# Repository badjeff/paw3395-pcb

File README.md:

# PAW3395 PCB

PixArt [**PAW3395DM-T6QU**](https://www.pixart.com/products-detail/129/PAW3395DM-T6QU) low power laser mouse sensor breakout board.

- Compatible to **PAW3950DM-T5QU**.
- Be operated with 3.3V voltage level ONLY.
- Outlined as narrow as possible for side mount horizontally and perpendicular on low profile keyboards.
- Developed for [zmk-paw3395-driver](https://github.com/badjeff/zmk-paw3395-driver) and [zmk-paw3950-driver](https://github.com/badjeff/zmk-paw3950-driver)

*Figure 1: Size comparing to Seeed XIAO BLE*

## PCB

Online preview avaliable [here](https://kicanvas.org/?github=https%3A%2F%2Fgithub.com%2Fbadjeff%2Fpaw3395-pcb), powered by [KiCanvas](https://github.com/theacodes/kicanvas).

*Figure 2: PCB edgecuts dimension*

*Figure 3: PCB 3D View - 1.6mm FR4*

### BOM

|Designator|Footprint|Quantity|Value|LCSC Part #|
|-|-|-|-|-|
|C1|SMD 0603|1|4.7uF||
|C11, C9|SMD 0603|2|1uF||
|C2, C4, C5|SMD 0603|3|100nF||
|C3, C6, C8|SMD 0603|3|10uF||
|C7|SMD 0603|1|22uF||
|C10|SMD 0603|1|DNI||
|R1|SMD 0603|1|10K|C25804|
|R2|SMD 0603|1|4.7|C23164|
|R3|SMD 0603|1|2M|C22976|
|U1|SOT-23-5|1|TLV74318PDBVR||
|U2|PAW3395DM-T6QU|1|PAW3395||
|  |PAW3950DM-T5QU|1|PAW3950||

- DNI: don't install.
- SMD 0603 (Imperial) aka 1608 Metric.
- ~~`U1` LDO can be replace by RT9193-18GB, change `C10` to 22nF.~~
- `U1` LDO can be replace by XC6219B182MR or TLV75519PDBVR
- `C1` can be replace by 3.3uF.
- For **PAW3395** Option
  * PAW3395DM-T6QU needs to be used with *compact* LOAE-LSI1 lens, or *chonky* LM19-LSI lens.
- For **PAW3950** Option
  * PAW3950DM-T5QU needs to be used with *compact* LOAE-LSI1 lens, or *chonky* LM19-LSI lens.
  * `R1` should be DNI
  * `R2` should be closed (with zero ohm resistor)
  * Pin 2 & 3 should be connecting with a 2.2uf capicator

*Figure 4: PAW3950 option

### Board Characteristics

- Copper layer count: 2
- Board thickness: 1.6 mm
- Board overall dimensions: 15.5 x 28 mm

### Voltage level config

- 3.3V logic
- VIN: 3.3V

## License

Available under the [CERN-OHL-P v2](/LICENSE) permissive license.

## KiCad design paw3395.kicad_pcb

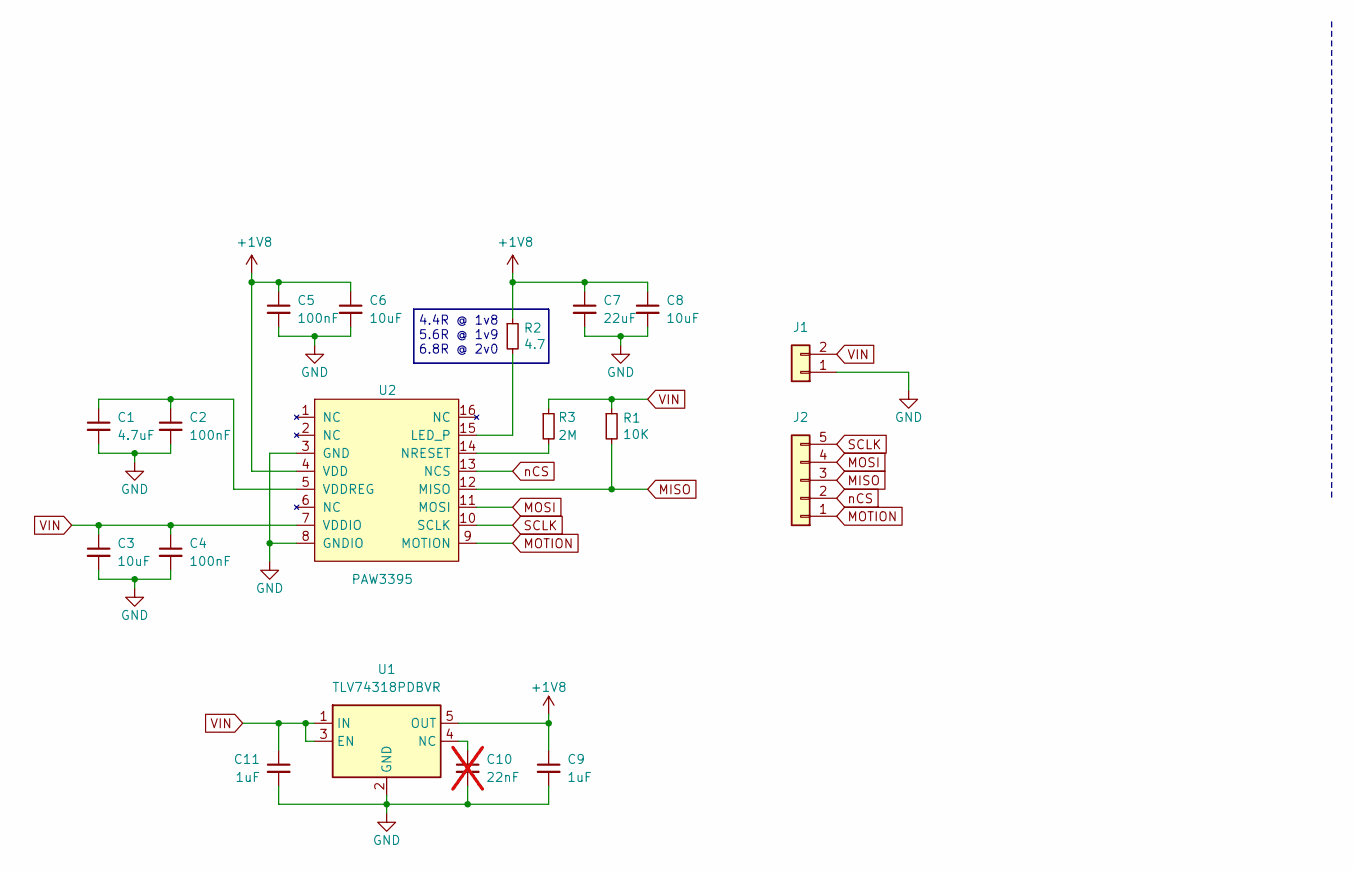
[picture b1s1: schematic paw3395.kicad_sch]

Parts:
C1: 4.7uF; C_0603_1608Metric
C2, C4, C5: 100nF; C_0603_1608Metric
C3, C6, C8: 10uF; C_0603_1608Metric
C7: 22uF; C_0603_1608Metric
C9, C11: 1uF; C_0603_1608Metric
C10: 22nF; C_0603_1608Metric; not fitted
J1: Conn_01x02; PinHeader_1x02_P2.54mm_Vertical
J2: Conn_01x05; PinHeader_1x05_P2.54mm_Vertical
R1: 10K; R_0603_1608Metric; LCSC C25804
R2: 4.7; R_0603_1608Metric; LCSC C23164
R3: 2M; R_0603_1608Metric; LCSC C22976
U1: TLV74318PDBVR; SOT-23-5_HandSoldering
U2: PAW3395

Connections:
+1V8: C5.1, C6.1, C7.1, C8.1, C9.1, R2.1, U1.5 (OUT), U2.4 (VDD)
GND: C1.2, C2.2, C3.2, C4.2, C5.2, C6.2, C7.2, C8.2, C9.2, C10.2, C11.2, J1.1, U1.2 (GND), U2.3 (GND), U2.8 (GNDIO)
MISO: J2.3, R1.2, U2.12 (MISO)
MOSI: J2.4, U2.11 (MOSI)
MOTION: J2.1, U2.9 (MOTION)
unnamed: C10.1, U1.4 (NC)
unnamed: R2.2, U2.15 (LED_P)
unnamed: R3.2, U2.14 (NRESET)
unnamed: C1.1, C2.1, U2.5 (VDDREG)
SCLK: J2.5, U2.10 (SCLK)
VIN: C3.1, C4.1, C11.1, J1.2, R1.1, R3.1, U1.1 (IN), U1.3 (EN), U2.7 (VDDIO)
nCS: J2.2, U2.13 (NCS)

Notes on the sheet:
4.4R @ 1v8 5.6R @ 1v9 6.8R @ 2v0

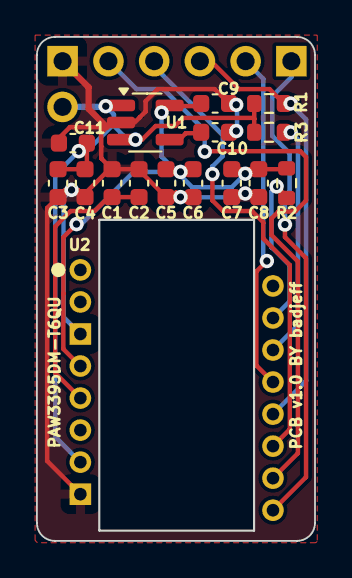
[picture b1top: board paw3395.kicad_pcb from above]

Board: 2 copper layers, 15.4 x 28.0 mm, 18 parts (0 on the bottom side), 12 nets.

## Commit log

2025-05-09 init commit
2025-05-20 add altrernative components
2025-11-09 fix typo
2026-06-18 ass PAW3950 option in readme
